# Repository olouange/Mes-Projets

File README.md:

# Mes Projets

Bienvenue dans ce dépôt, qui regroupe une sélection de mes projets personnels et académiques.  
La majorité de ces projets sont développés en **Python** ou **C/C++**, et certains incluent des **Makefiles** afin d’automatiser le processus de compilation.

| Projet | Description |
|--------|-------------|
| **Projet Client-Serveur** | Implémentation d’une architecture client-serveur avec gestion des échanges réseau. |
| **Projet Gyro Boy** | Contrôle et stabilisation d’un robot Gyro Boy à l’aide d’un capteur gyroscopique. |
| **Projet Pami 4** | Développement d’un robot autonome pour la Coupe de France de Robotique. Le projet repose sur l’automatisation des déplacements et l’évitement d’obstacles grâce à des capteurs à ultrasons et des matrices de détection. |
| **Projet Six qui Prend** | Version numérique du jeu de cartes *6 qui prend*, développée pour s’entraîner à la programmation. |
| **Projet Stabilisateur pour Robot à Deux Roues** | Conception d’un algorithme de stabilisation pour un robot à deux roues auto-équilibré. |
| **Projet Puissance 4** | Adaptation numérique du jeu *Puissance 4* avec une interface interactive. |

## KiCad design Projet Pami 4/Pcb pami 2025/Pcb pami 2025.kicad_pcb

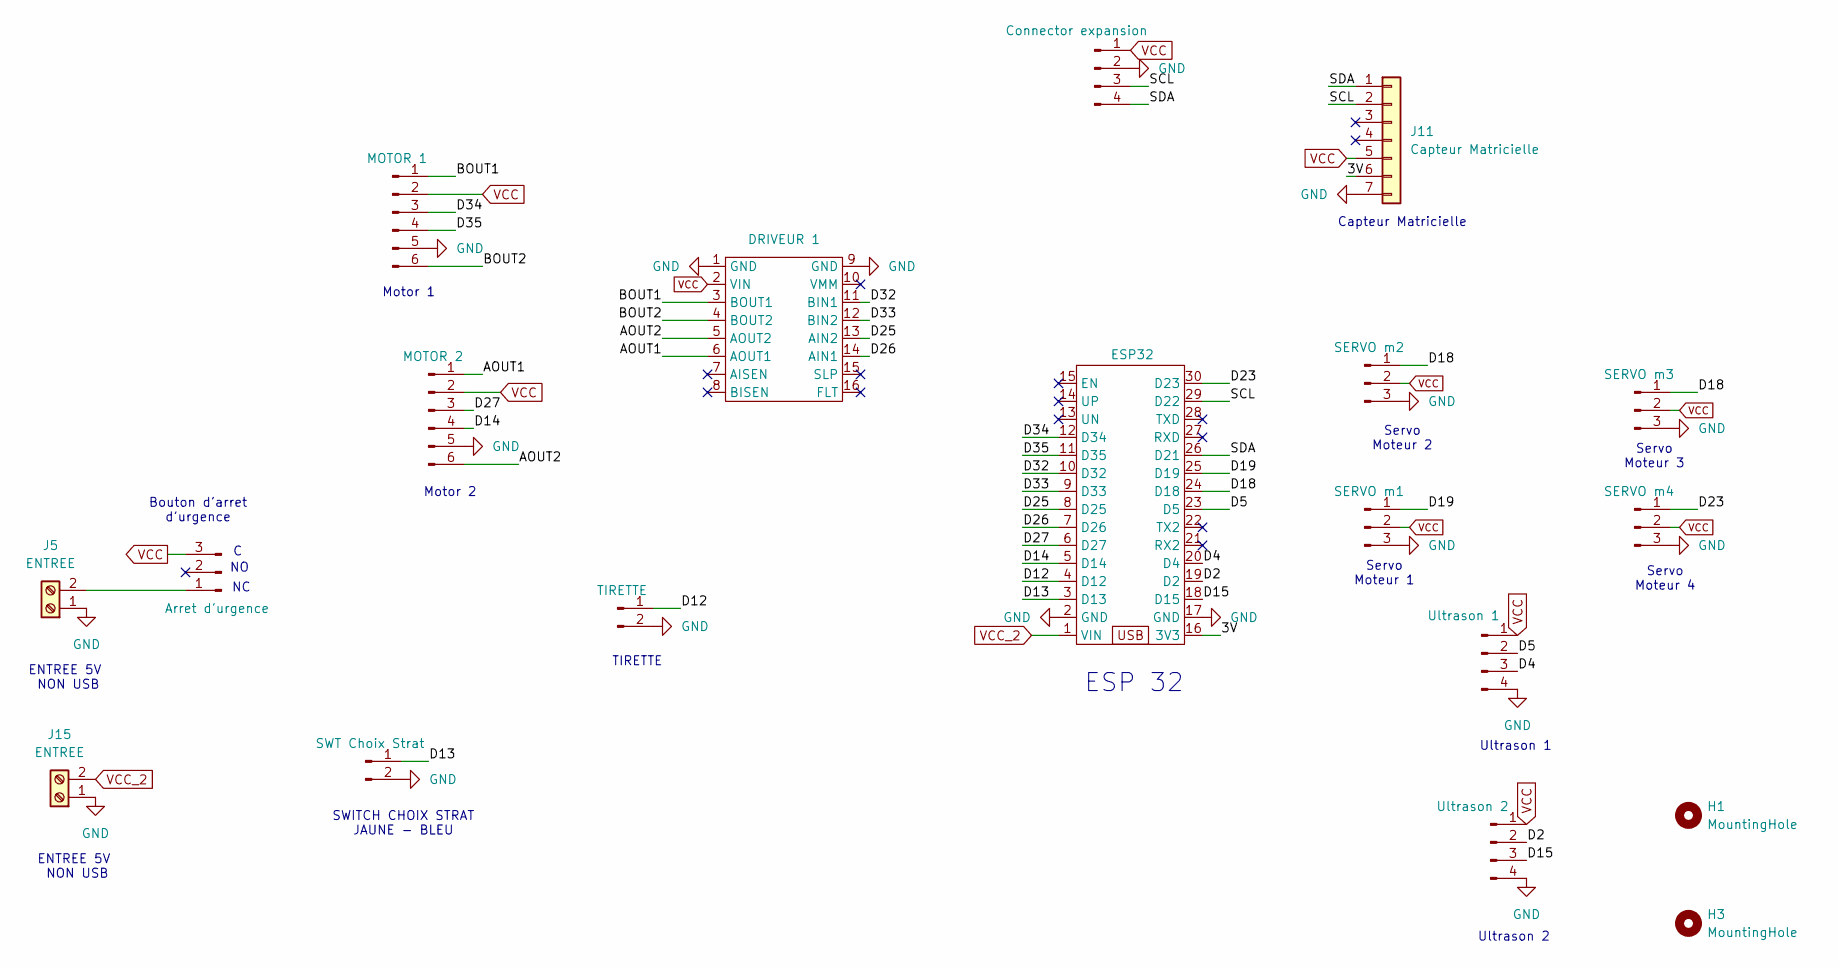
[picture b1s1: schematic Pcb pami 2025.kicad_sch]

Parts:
H1, H3: MountingHole; MountingHole_3.2mm_M3
J1: SERVO m1; PinHeader_1x03_P2.54mm_Vertical
J2: SERVO m2; PinHeader_1x03_P2.54mm_Vertical
J3: SERVO m4; PinHeader_1x03_P2.54mm_Vertical
J4: Ultrason 1; PinHeader_1x04_P2.54mm_Vertical
J5, J15: ENTREE; PinHeader_1x02_P2.54mm_Vertical
J6: Arret d'urgence; PinSocket_1x03_P2.54mm_Vertical
J7: TIRETTE; PinHeader_1x02_P2.54mm_Vertical
J8: MOTOR 1; PinHeader_1x06_P2.54mm_Vertical
J9: MOTOR 2; PinHeader_1x06_P2.54mm_Vertical
J10: Ultrason 2; PinHeader_1x04_P2.54mm_Vertical
J11: Capteur Matricielle; PinHeader_1x07_P2.54mm_Vertical
J12: SERVO m3; PinHeader_1x03_P2.54mm_Vertical
J13: SWT Choix Strat; PinHeader_1x02_P2.54mm_Vertical
J14: Connector expansion; PinHeader_1x04_P2.54mm_Vertical
U1: ESP32; esp32_wroom32
U2: DRIVEUR 1; DRV8833

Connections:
/3V: J11.6, U1.16 (3V3)
/AOUT1: J9.1, U2.6 (AOUT1)
/AOUT2: J9.6, U2.5 (AOUT2)
/BOUT1: J8.1, U2.3 (BOUT1)
/BOUT2: J8.6, U2.4 (BOUT2)
/D2: J10.2, U1.19 (D2)
/D4: J4.3, U1.20 (D4)
/D5: J4.2, U1.23 (D5)
/D12: J7.1, U1.4 (D12)
/D13: J13.1, U1.3 (D13)
/D14: J9.4, U1.5 (D14)
/D15: J10.3, U1.18 (D15)
/D18: J2.1, J12.1, U1.24 (D18)
/D19: J1.1, U1.25 (D19)
/D23: J3.1, U1.30 (D23)
/D25: U1.8 (D25), U2.13 (AIN2)
/D26: U1.7 (D26), U2.14 (AIN1)
/D27: J9.3, U1.6 (D27)
/D32: U1.10 (D32), U2.11 (BIN1)
/D33: U1.9 (D33), U2.12 (BIN2)
/D34: J8.3, U1.12 (D34)
/D35: J8.4, U1.11 (D35)
/SCL: J11.2, J14.3, U1.29 (D22)
/SDA: J11.1, J14.4, U1.26 (D21)
GND: J1.3, J2.3, J3.3, J4.4, J5.1, J7.2, J8.5, J9.5, J10.4, J11.7, J12.3, J13.2, J14.2, J15.1, U1.2 (GND), U1.17 (GND), U2.1 (GND), U2.9 (GND)
unnamed: J5.2, J6.1

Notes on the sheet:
Ultrason 2
ENTREE 5V NON USB
Bouton d'arret d'urgence
Motor 2
Motor 1
Ultrason 1
Servo Moteur 1
Servo Moteur 4
SWITCH CHOIX STRAT JAUNE - BLEU
Servo Moteur 3
TIRETTE
ESP 32
Servo Moteur 2
Capteur Matricielle

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
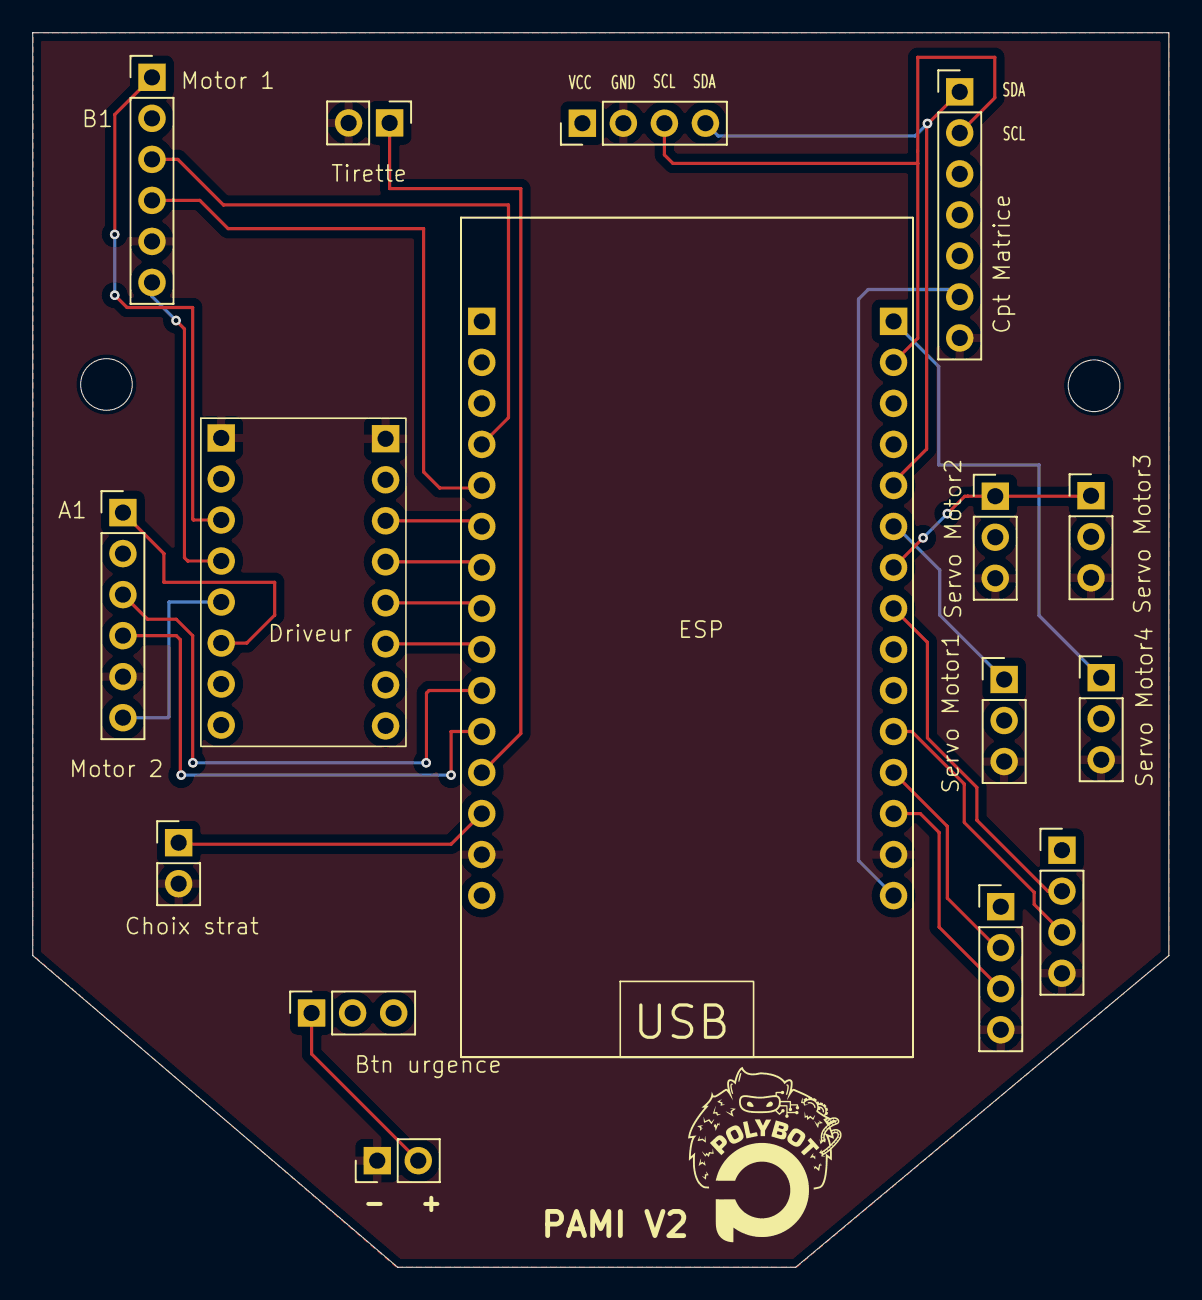
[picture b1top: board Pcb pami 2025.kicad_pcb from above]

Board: 2 copper layers, 70.4 x 76.5 mm, 18 parts (0 on the bottom side), 27 nets.

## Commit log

2025-08-21 Mise à jour de tous les projets
